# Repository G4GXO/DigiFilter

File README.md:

# DigiFilter
Audio Processor

The DigiFilter is an in-line audio DSP module which features a filter with adjustable stop bands (0-4kHz), an NLMS Denoiser, Autonotch and Binaural operation. It
is intended as an add on accessory for radio transceivers/receivers to improve reception. The DigiFilter hardware and software presented here is for personal, 
non-commercial use as described in the Creative Commons License. See the Licence folder for a copy of the licence.

PW Readers!

Several late changes have been made to the software which could not be included in the PW article. These are summarised below;

Denoiser. Press and release the encoder to toggle the Denoiser on and off. With the Denoiser enabled, rotating the encoder steps through 5 levels of denoising. 
To exit Denoiser adjustment whilst leaving the Denoiser active, press and hold the encoder until the Morse "D" Denoiser menu announcement is heard. Rotating the 
encoder now allows navigation at menu level. With the Denoiser toggled off, normal menu navigation is active.

Binaural. The Binaural mode no longer supports an adjustable delay, this was found to offer little benefit and caused confusion when trying to use the menu 
system. Binaural mode is now toggled on or off by the encoder press/release operation. With Binaural active, rotating the encoder adjusts left and right channel
balance. Accordingly, menu options "T" and "Q" are no longer used. To exit Binaural mode leaving it active, press and hold the encoder until the Morse "B" Binaural 
menu announcement is heard. With Binaural toggled off, turning the encoder resumes normal menu navigation.

Menu Navigation. With the exception of the Filter Upper and Lower corner frequency adjsutments, the new menu structure is flat hence the menu "M" announcement is
no longer in use. In any menu, irrespective of that menu item's operation, a press and hold will return to navigation from current menu option which will be 
announced in Morse.

New Hardware Options. During use it was found that in some function and indication of whether or not that function was active would have been useful. This was
particularly the case for the Autonotch, which when engaged does not colour the audio and with no indication that it is enabled, could present some confusion.
Three additional outputs are now available on spare processor pins whose state goes high for a function being engaged and low for disengaged. These pins may
be used to drive low current indicator LEDs via suitable resistors, (around 220R -330R). The pins are as follows;

Denoiser State    Pin 14 RB5

Autonotch State   Pin 11 RB4

Binaural State    Pin 7  RB3

If you use these be sure not to cause solder bridges with adjacent pins!

Morse Announcements. The morse announcements used to indicate menu position and certain actions are described below.

F (di di dah dit) Filter – Press/Rel to enter Upper Passband Mode, Press/Hold to return to menu navigation.

  U (di di dah) Filter Upper Passband Mode (Press/Rel for lower)
  
  L (di dah di dit) Filter Lower Passband Mode (Press/Rel for upper)

A (di dah) Autonotch – Press/Rel to toggle on/off.  No adjustment, turn encoder to change menu.

D (dah di dit) Denoiser – Press/Rel to toggle on/off.  Turn to change denoiser levels. Press/Hold to exit to menu leaving Denoiser enabled.

B (dah di di dit) Binaural – Press/Rel to toggle on/off, turn for balance. Press/Hold to exit to menu leaving Binaural enabled.

P (di dah dah dit) Save filter against selected preset. Upon save a confirmation "K" will be heard.

G (dah da dit) Tone Gain – Press/Rel to enter (Press/hold to save and exit)

E (dit)  Adjustment Step notification

S (di di dit) Limit reached, High pitch= upper, low pitch= lower

K (dah di dah) Preset storage success

Ron Taylor G4GXO

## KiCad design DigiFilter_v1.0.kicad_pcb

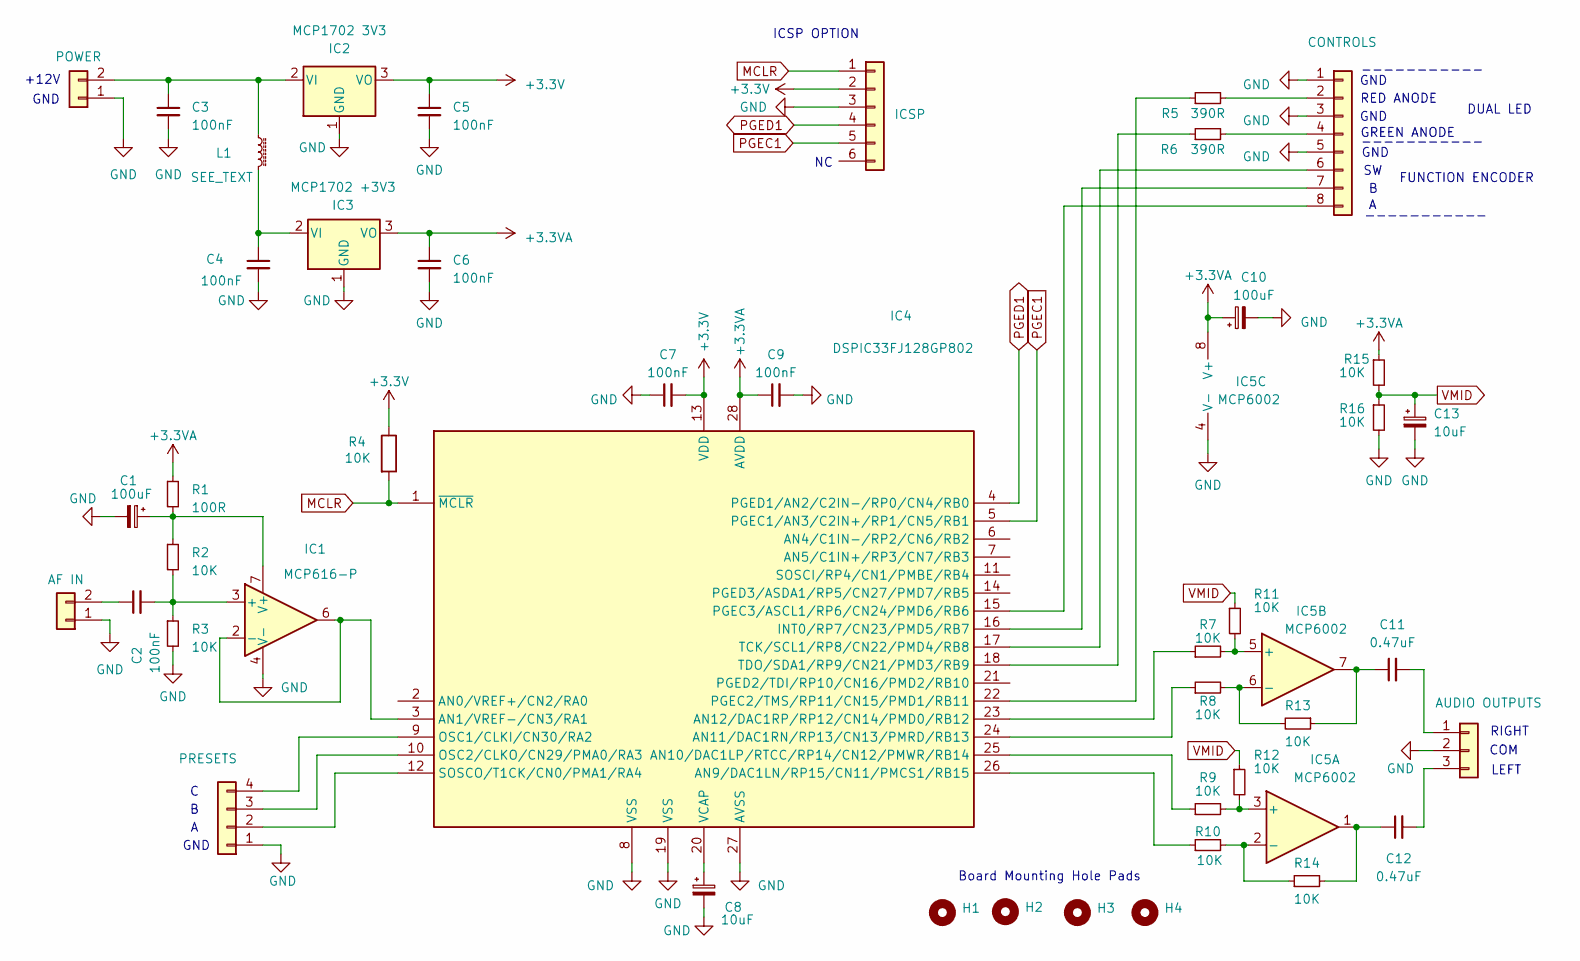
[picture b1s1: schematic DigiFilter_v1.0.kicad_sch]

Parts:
C1, C10: 100uF; CP_Radial_D6.3mm_P2.50mm
C2, C3, C4, C5, C6, C7, C9: 100nF; C_Disc_D5.0mm_W2.5mm_P2.50mm
C8, C13: 10uF; CP_Radial_D5.0mm_P2.50mm
C11, C12: 0.47uF; C_Disc_D6.0mm_W2.5mm_P5.00mm
H1, H2, H3, H4: MountingHole; MountingHole_2.7mm_M2.5
IC1: MCP616-P; DIP-8_W7.62mm_LongPads
IC2: MCP1702 3V3; TO-92_Inline
IC3: MCP1702 +3V3; TO-92_Inline
IC4: DSPIC33FJ128GP802; DIP-28_W7.62mm_LongPads
IC5: MCP6002; DIP-8_W7.62mm_LongPads
J1: AF IN; Molex_KK-254_AE-6410-02A_1x02_P2.54mm_Vertical
J2: POWER; Molex_KK-254_AE-6410-02A_1x02_P2.54mm_Vertical
J3: PRESETS; Molex_KK-254_AE-6410-04A_1x04_P2.54mm_Vertical
J4: ICSP; Molex_KK-254_AE-6410-06A_1x06_P2.54mm_Vertical
J5: CONTROLS; Molex_KK-254_AE-6410-08A_1x08_P2.54mm_Vertical
J6: AUDIO OUTPUTS; Molex_KK-254_AE-6410-03A_1x03_P2.54mm_Vertical
L1: SEE_TEXT; L_Axial_L5.3mm_D2.2mm_P7.62mm_Horizontal_Vishay_IM-1
R1: 100R; R_Axial_DIN0207_L6.3mm_D2.5mm_P7.62mm_Horizontal
R2, R3, R4, R7, R8, R9, R10, R11, R12, R13, R14, R15, R16: 10K; R_Axial_DIN0207_L6.3mm_D2.5mm_P7.62mm_Horizontal
R5, R6: 390R; R_Axial_DIN0207_L6.3mm_D2.5mm_P7.62mm_Horizontal

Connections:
+3.3V: C5.1, C7.2, IC2.3 (VO), IC4.13 (VDD), J4.2, R4.1
+3.3VA: C6.1, C9.1, C10.1, IC3.3 (VO), IC4.28 (AVDD), IC5.8 (V+), R1.1, R15.1
GND: C1.2, C3.2, C4.2, C5.2, C6.2, C7.1, C8.2, C9.2, C10.2, C13.2, IC1.4 (V-), IC2.1 (GND), IC3.1 (GND), IC4.8 (VSS), IC4.19 (VSS), IC4.27 (AVSS), IC5.4 (V-), J1.1, J2.1, J3.1, J4.3, J5.1, J5.3, J5.5, J6.2, R3.2, R16.2
MCLR: IC4.1 (~MCLR), J4.1, R4.2
unnamed: C11.1, IC5.7, R13.1
unnamed: C12.1, IC5.1, R14.2
unnamed: C2.2, IC1.3 (+), R2.2, R3.1
unnamed: IC1.2 (-), IC1.6, IC4.3 (AN1/VREF-/CN3/RA1)
unnamed: C1.1, IC1.7 (V+), R1.2, R2.1
unnamed: C3.1, IC2.2 (VI), J2.2, L1.1
unnamed: C4.1, IC3.2 (VI), L1.2
unnamed: IC4.26 (AN9/DAC1LN/RP15/CN11/PMCS1/RB15), R10.1
unnamed: IC4.25 (AN10/DAC1LP/RTCC/RP14/CN12/PMWR/RB14), R9.1
unnamed: IC4.24 (AN11/DAC1RN/RP13/CN13/PMRD/RB13), R8.1
unnamed: IC4.23 (AN12/DAC1RP/RP12/CN14/PMD0/RB12), R7.1
unnamed: IC4.16 (INT0/RP7/CN23/PMD5/RB7), J5.7
unnamed: IC4.9 (OSC1/CLKI/CN30/RA2), J3.4
unnamed: IC4.10 (OSC2/CLKO/CN29/PMA0/RA3), J3.3
unnamed: IC4.22 (PGEC2/TMS/RP11/CN15/PMD1/RB11), R5.1
unnamed: IC4.15 (PGEC3/ASCL1/RP6/CN24/PMD6/RB6), J5.8
unnamed: IC4.12 (SOSCO/T1CK/CN0/PMA1/RA4), J3.2
unnamed: IC4.17 (TCK/SCL1/RP8/CN22/PMD4/RB8), J5.6
unnamed: IC4.18 (TDO/SDA1/RP9/CN21/PMD3/RB9), R6.1
unnamed: C8.1, IC4.20 (VCAP)
unnamed: IC5.3 (+), R9.2, R12.2
unnamed: IC5.2 (-), R10.2, R14.1
unnamed: IC5.5 (+), R7.2, R11.2
unnamed: IC5.6 (-), R8.2, R13.2
unnamed: C2.1, J1.2
unnamed: J5.2, R5.2
unnamed: J5.4, R6.2
unnamed: C11.2, J6.1
unnamed: C12.2, J6.3
PGEC1: IC4.5 (PGEC1/AN3/C2IN+/RP1/CN5/RB1), J4.5
PGED1: IC4.4 (PGED1/AN2/C2IN-/RP0/CN4/RB0), J4.4
VMID: C13.1, R11.1, R12.1, R15.2, R16.1

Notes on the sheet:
LEFT
+12V
RED ANODE
COM
GND
RIGHT
ICSP OPTION
FUNCTION ENCODER
Board Mounting Hole Pads
DUAL LED
-----------
GREEN ANODE

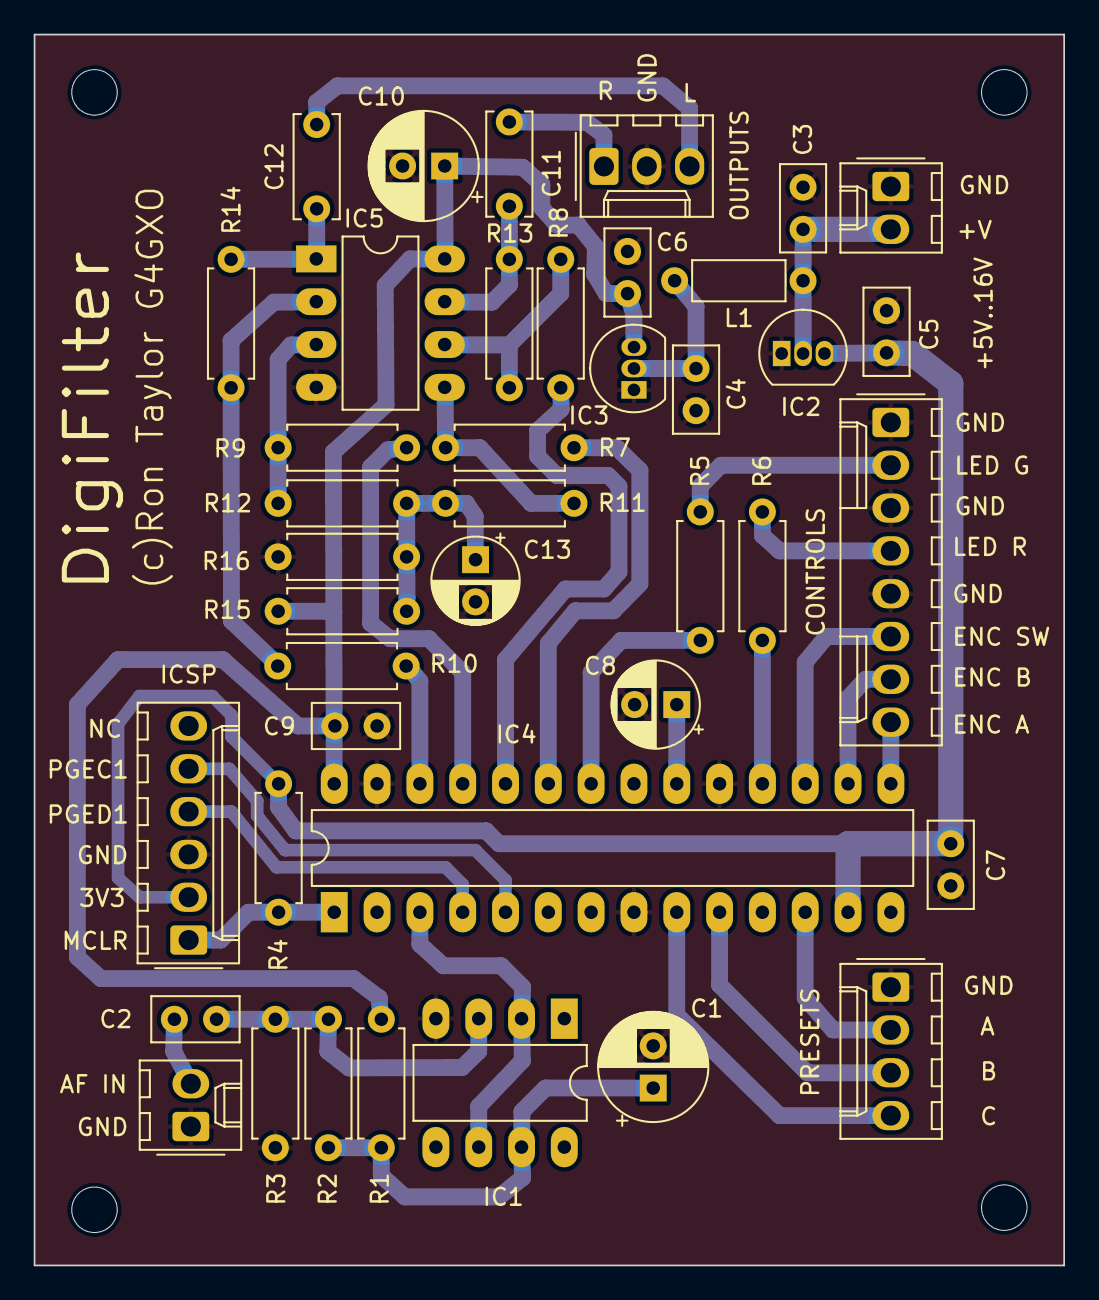
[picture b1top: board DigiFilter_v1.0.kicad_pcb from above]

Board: 2 copper layers, 61.1 x 73.0 mm, 45 parts (0 on the bottom side), 36 nets.

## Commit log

2024-06-15 Create LICENSE
2024-10-31 Update LICENSE
2025-02-09 Update Main.h
    Red and Green LED pins swapped to align with PCB labelling.
